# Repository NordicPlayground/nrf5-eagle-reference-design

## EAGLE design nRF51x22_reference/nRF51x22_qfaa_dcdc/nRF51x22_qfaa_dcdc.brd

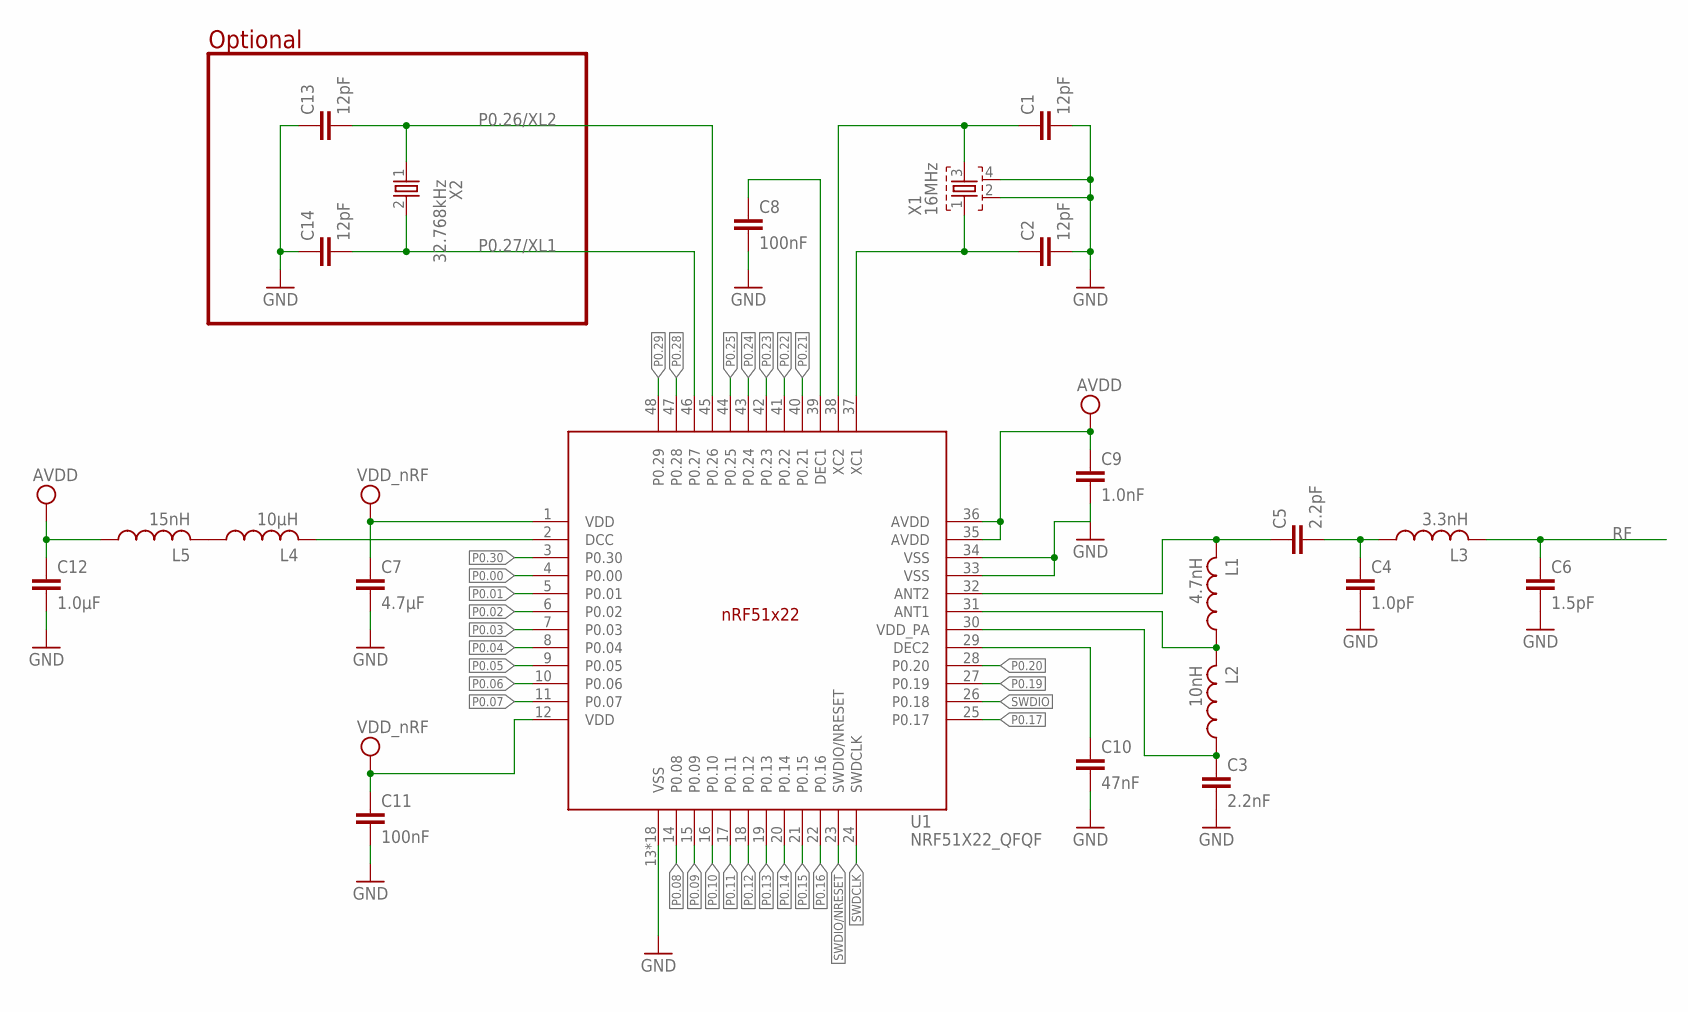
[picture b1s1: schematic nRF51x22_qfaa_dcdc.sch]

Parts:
C1, C2, C13, C14: 12pF; RESC0402_N
C3: 2.2nF; RESC0402_N
C4: 1.0pF; RESC0402_N
C5: 2.2pF; RESC0402_N
C6: 1.5pF; RESC0402_N
C7: 4.7µF; RESC0603_N
C8, C11: 100nF; RESC0402_N
C9: 1.0nF; RESC0402_N
C10: 47nF; RESC0402_N
C12: 1.0µF; RESC0603_N
L1: 4.7nH; RESC0402_N
L2: 10nH; RESC0402_N
L3: 3.3nH; RESC0402_N
L4: 10µH; RESC0603_N
L5: 15nH; RESC0402_N
U1: NRF51X22_QFQF; QFN40P600X600X90-48_N
X1: 16MHz; BT-XTAL_2016_N
X2: 32.768kHz; XTAL_3215_N

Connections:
AVDD: C9.1, C12.1, L5.1, U1.35 (AVDD), U1.36 (AVDD)
GND: C1.2, C2.2, C3.2, C4.2, C6.2, C7.2, C8.2, C9.2, C10.2, C11.2, C12.2, C13.1, C14.1, U1.13 (VSS), U1.33 (VSS), U1.34 (VSS), U1.PAD (VSS), U1.PAD@VIA01 (VSS), U1.PAD@VIA02 (VSS), U1.PAD@VIA03 (VSS), U1.PAD@VIA04 (VSS), U1.PAD@VIA05 (VSS), U1.PAD@VIA06 (VSS), U1.PAD@VIA07 (VSS), U1.PAD@VIA08 (VSS), U1.PAD@VIA09 (VSS), U1.PAD@VIA10 (VSS), U1.PAD@VIA11 (VSS), U1.PAD@VIA12 (VSS), U1.PAD@VIA13 (VSS), U1.PAD@VIA14 (VSS), U1.PAD@VIA15 (VSS), U1.PAD@VIA16 (VSS), X1.2, X1.4
unnamed: L1.1, L2.2, U1.31 (ANT1)
unnamed: L4.1, L5.2
unnamed: C1.1, U1.38 (XC2), X1.3
unnamed: L4.2, U1.2 (DCC)
unnamed: C10.1, U1.29 (DEC2)
unnamed: C8.1, U1.39 (DEC1)
unnamed: C3.1, L2.1, U1.30 (VDD_PA)
unnamed: C5.1, L1.2, U1.32 (ANT2)
unnamed: C4.1, C5.2, L3.1
P0.00: U1.4 (P0.00)
P0.01: U1.5 (P0.01)
P0.02: U1.6 (P0.02)
P0.03: U1.7 (P0.03)
P0.04: U1.8 (P0.04)
P0.05: U1.9 (P0.05)
P0.06: U1.10 (P0.06)
P0.07: U1.11 (P0.07)
P0.08: U1.14 (P0.08)
P0.09: U1.15 (P0.09)
P0.10: U1.16 (P0.10)
P0.11: U1.17 (P0.11)
P0.12: U1.18 (P0.12)
P0.13: U1.19 (P0.13)
P0.14: U1.20 (P0.14)
P0.15: U1.21 (P0.15)
P0.16: U1.22 (P0.16)
P0.17: U1.25 (P0.17)
P0.19: U1.27 (P0.19)
P0.20: U1.28 (P0.20)
P0.21: U1.40 (P0.21)
P0.22: U1.41 (P0.22)
P0.23: U1.42 (P0.23)
P0.24: U1.43 (P0.24)
P0.25: U1.44 (P0.25)
P0.26/XL2: C13.2, U1.45 (P0.26), X2.1
P0.27/XL1: C14.2, U1.46 (P0.27), X2.2
P0.28: U1.47 (P0.28)
P0.29: U1.48 (P0.29)
P0.30: U1.3 (P0.30)
RF: C6.1, L3.2
SWDCLK: U1.24 (SWDCLK)
SWDIO: U1.26 (P0.18)
SWDIO/NRESET: U1.23 (SWDIO/NRESET)
VDD_NRF: C7.1, C11.1, U1.1 (VDD), U1.12 (VDD)
X1: C2.1, U1.37 (XC1), X1.1

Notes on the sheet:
Optional

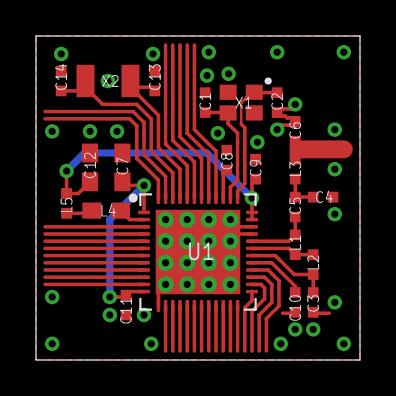
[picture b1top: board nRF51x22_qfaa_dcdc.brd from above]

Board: 2 copper layers, 18.0 x 18.0 mm, 22 parts (0 on the bottom side), 16 nets.

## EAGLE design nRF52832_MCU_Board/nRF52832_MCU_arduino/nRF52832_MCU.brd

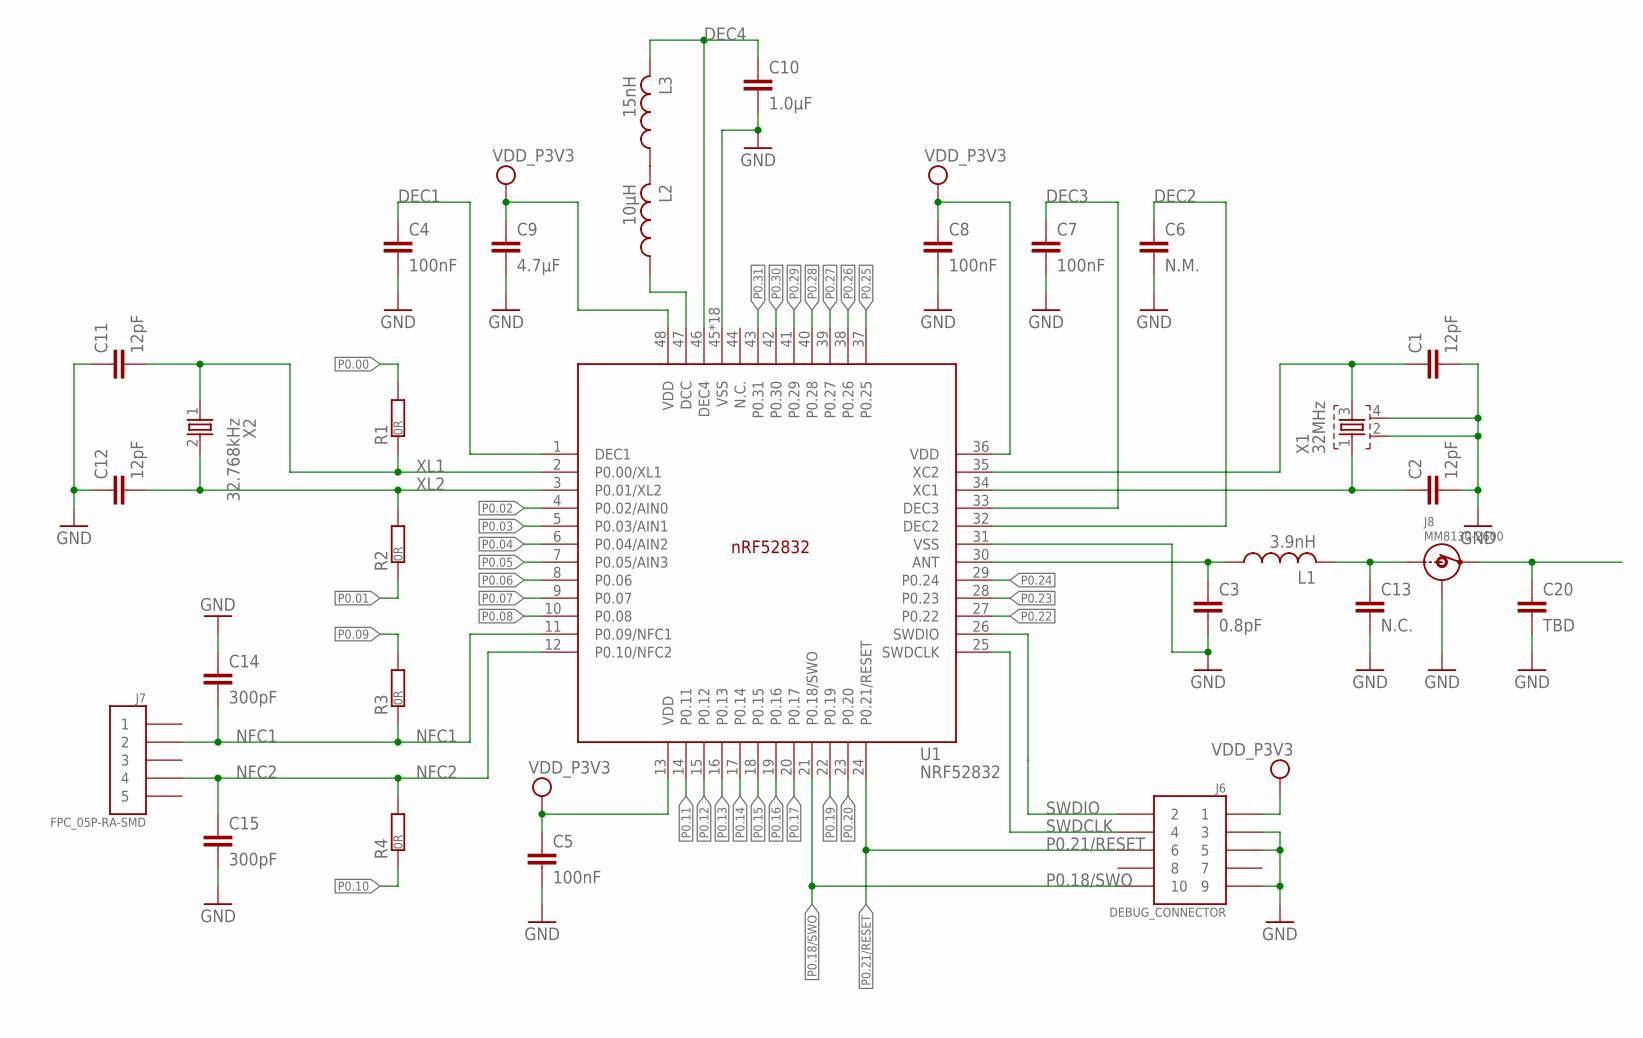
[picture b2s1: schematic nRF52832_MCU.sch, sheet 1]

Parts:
C1, C2, C11, C12: 12pF; RESC0402_N
C3: 0.8pF; RESC0402_N
C4, C5, C7, C8: 100nF; RESC0402_N
C6: N.M.; RESC0402_N
C9: 4.7µF; RESC0603_N
C10: 1.0µF; RESC0603_N
C13: N.C.; RESC0402_N
C14, C15: 300pF; RESC0402_N
C20: TBD; RESC0402_N
J6: DEBUG_CONNECTOR; HDRV127P5X2-10_N
J7: FPC_05P-RA-SMD
J8: MM8130-2600
L1: 3.9nH; RESC0402_N
L2: 10µH; RESC0603_N
L3: 15nH; RESC0402_N
R1, R2, R3, R4: 0R; RESC0402_N
U1: NRF52832; QFN40P600X600X90-48_N
X1: 32MHz; BT-XTAL_2016_N
X2: 32.768kHz; XTAL_3215_N

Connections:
ANT: C3.1, L1.1, U1.30 (ANT)
DEC1: C4.1, U1.1 (DEC1)
DEC2: C6.1, U1.32 (DEC2)
DEC3: C7.1, U1.33 (DEC3)
DEC4: C10.1, L3.2, U1.46 (DEC4)
GND: C1.2, C2.2, C3.2, C4.2, C5.2, C6.2, C7.2, C8.2, C9.2, C10.2, C11.1, C12.1, C13.2, C14.1, C15.2, C20.2, J6.3, J6.5, J6.9, J8.1, J8.2, J8.3, J8.4, U1.31 (VSS), U1.45 (VSS), U1.PAD (VSS), U1.PAD@VIA01 (VSS), U1.PAD@VIA02 (VSS), U1.PAD@VIA03 (VSS), U1.PAD@VIA04 (VSS), U1.PAD@VIA05 (VSS), U1.PAD@VIA06 (VSS), U1.PAD@VIA07 (VSS), U1.PAD@VIA08 (VSS), U1.PAD@VIA09 (VSS), U1.PAD@VIA10 (VSS), U1.PAD@VIA11 (VSS), U1.PAD@VIA12 (VSS), U1.PAD@VIA13 (VSS), U1.PAD@VIA14 (VSS), U1.PAD@VIA15 (VSS), U1.PAD@VIA16 (VSS), X1.2, X1.4; also elsewhere on the board
unnamed: C20.1, J8.OUT
unnamed: L2.2, L3.1
unnamed: C1.1, U1.35 (XC2), X1.3
unnamed: L2.1, U1.47 (DCC)
unnamed: C13.1, J8.IN, L1.2
NFC1: C14.2, J7.2, R3.1, U1.11 (P0.09/NFC1)
NFC2: C15.1, J7.4, R4.2, U1.12 (P0.10/NFC2)
P0.00: R1.2
P0.01: R2.1
P0.02: U1.4 (P0.02/AIN0)
P0.03: U1.5 (P0.03/AIN1)
P0.04: U1.6 (P0.04/AIN2)
P0.05: U1.7 (P0.05/AIN3)
P0.06: U1.8 (P0.06); also elsewhere on the board
P0.07: U1.9 (P0.07); also elsewhere on the board
P0.08: U1.10 (P0.08); also elsewhere on the board
P0.09: R3.2
P0.10: R4.1
P0.11: U1.14 (P0.11)
P0.12: U1.15 (P0.12)
P0.13: U1.16 (P0.13)
P0.14: U1.17 (P0.14)
P0.15: U1.18 (P0.15)
P0.16: U1.19 (P0.16)
P0.17: U1.20 (P0.17)
P0.18/SWO: J6.10, U1.21 (P0.18/SWO)
P0.19: U1.22 (P0.19)
P0.20: U1.23 (P0.20)
P0.21/RESET: J6.6, U1.24 (P0.21/RESET); also elsewhere on the board
P0.22: U1.27 (P0.22)
P0.23: U1.28 (P0.23)
P0.24: U1.29 (P0.24)
P0.25: U1.37 (P0.25)
P0.26: U1.38 (P0.26)
P0.27: U1.39 (P0.27)
P0.28: U1.40 (P0.28)
P0.29: U1.41 (P0.29)
P0.30: U1.42 (P0.30)
P0.31: U1.43 (P0.31)
SWDCLK: J6.4, U1.25 (SWDCLK)
SWDIO: J6.2, U1.26 (SWDIO)
VDD_P3V3: C5.1, C8.1, C9.1, J6.1, U1.13 (VDD), U1.36 (VDD), U1.48 (VDD); also elsewhere on the board
X1: C2.1, U1.34 (XC1), X1.1
XL1: C11.2, R1.1, U1.2 (P0.00/XL1), X2.1
XL2: C12.2, R2.2, U1.3 (P0.01/XL2), X2.2

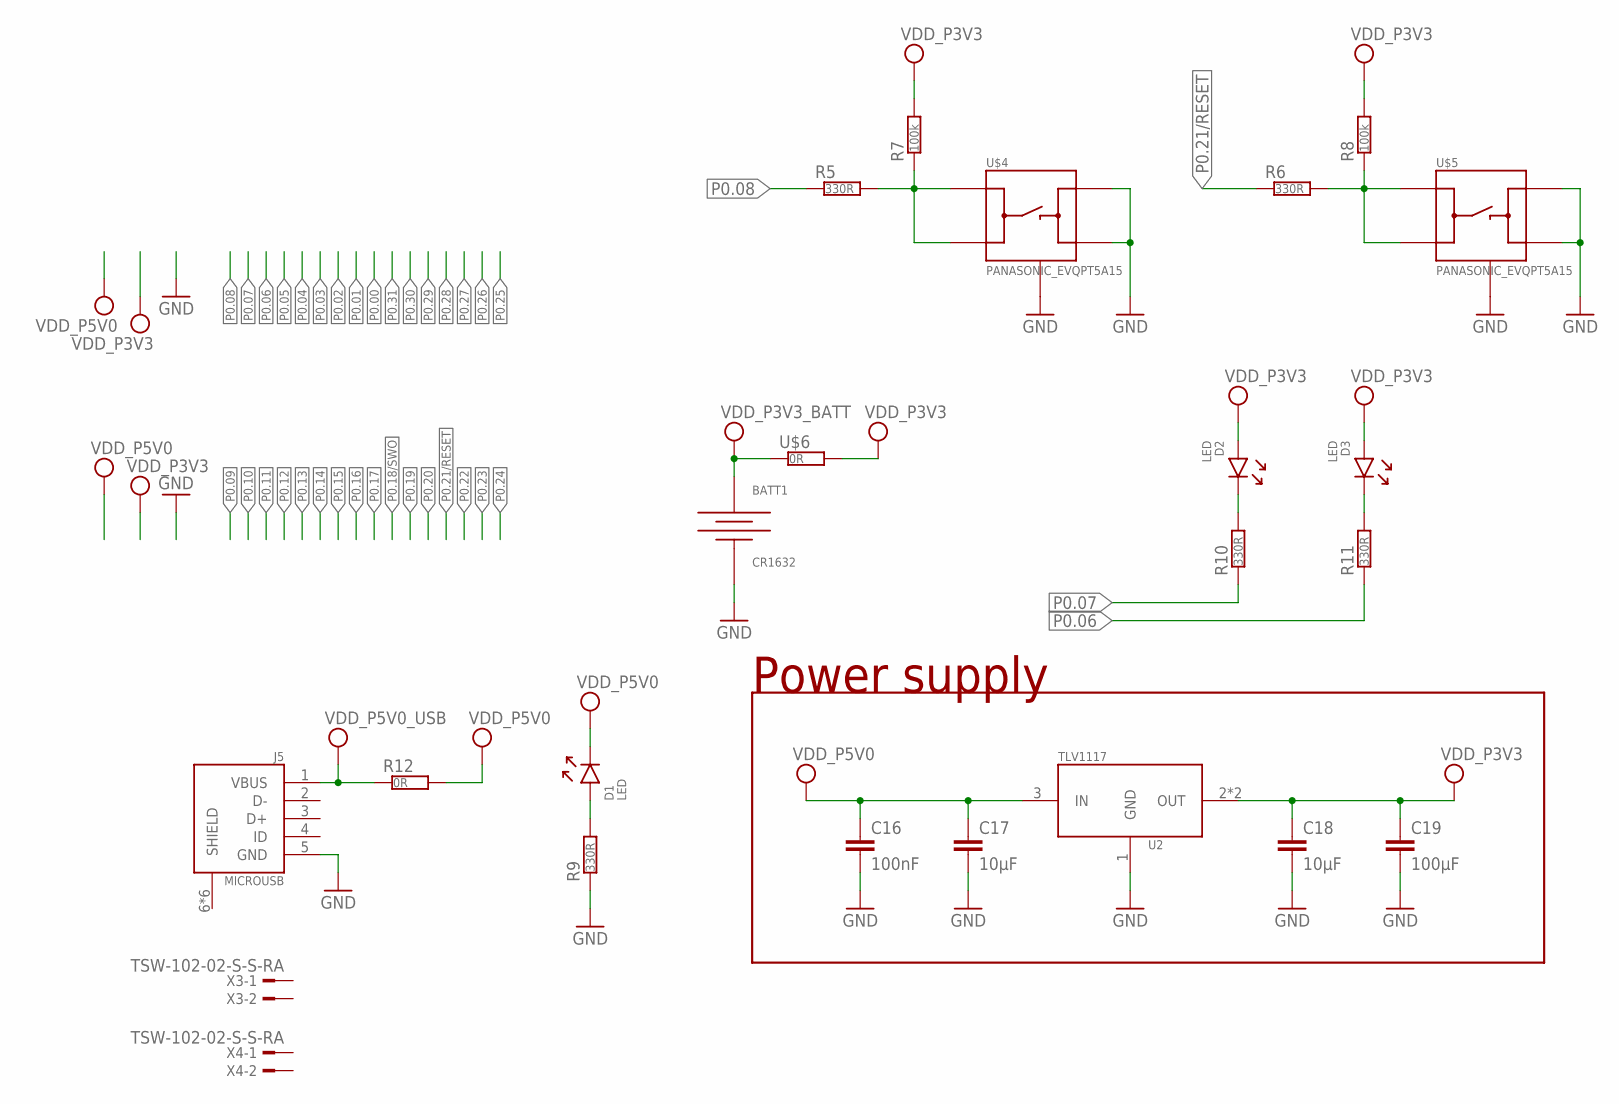
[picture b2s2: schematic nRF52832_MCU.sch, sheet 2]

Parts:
BATT1: CR1632; CR1632_HOLDER_TH
C16: 100nF; RESC0402_N
C17, C18: 10µF; RESC0603_N
C19: 100µF; RESC0805_N
D1, D2, D3: LED; DIOC0603_N
J5: MICROUSB; USB-MICRO-B-RA-SMD-PIP
R5, R6, R9, R10, R11: 330R; RESC0402_N
R7, R8: 100k; RESC0402_N
R12: 0R; RESC0402_N
U2: TLV1117; SOT220P700-4_N
U$4, U$5: PANASONIC_EVQPT5A15
U$6: 0R; RESC0402_N
X3, X4: TSW-102-02-S-S-RA

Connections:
GND: BATT1.1 (-), C16.2, C17.2, C18.2, C19.2, J5.5 (GND), R9.1, U2.1 (GND), U$4.3 (B), U$4.4 (B'), U$4.5 (GND), U$4.6 (GND), U$5.3 (B), U$5.4 (B'), U$5.5 (GND), U$5.6 (GND); also elsewhere on the board
unnamed: R6.2, R8.1, U$5.1 (A), U$5.2 (A')
unnamed: R5.2, R7.1, U$4.1 (A), U$4.2 (A')
unnamed: D2.1 (C), R10.2
unnamed: D3.1 (C), R11.2
P0.06: R11.1; also elsewhere on the board
P0.07: R10.1; also elsewhere on the board
P0.08: R5.1; also elsewhere on the board
P0.21/RESET: R6.1; also elsewhere on the board
VCC_P5V0_USB: J5.1 (VBUS), R12.1
VDD_LED: D1.2 (A), R9.2
VDD_P3V3: C18.1, C19.1, D2.2 (A), D3.2 (A), R7.2, R8.2, U2.2 (OUT), U2.4 (OUT), U$6.2; also elsewhere on the board
VDD_P3V3_BATT: BATT1.2 (+), BATT1.3 (+), U$6.1
VDD_P5V0: C16.1, C17.1, D1.1 (C), R12.2, U2.3 (IN)

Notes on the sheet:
Power supply

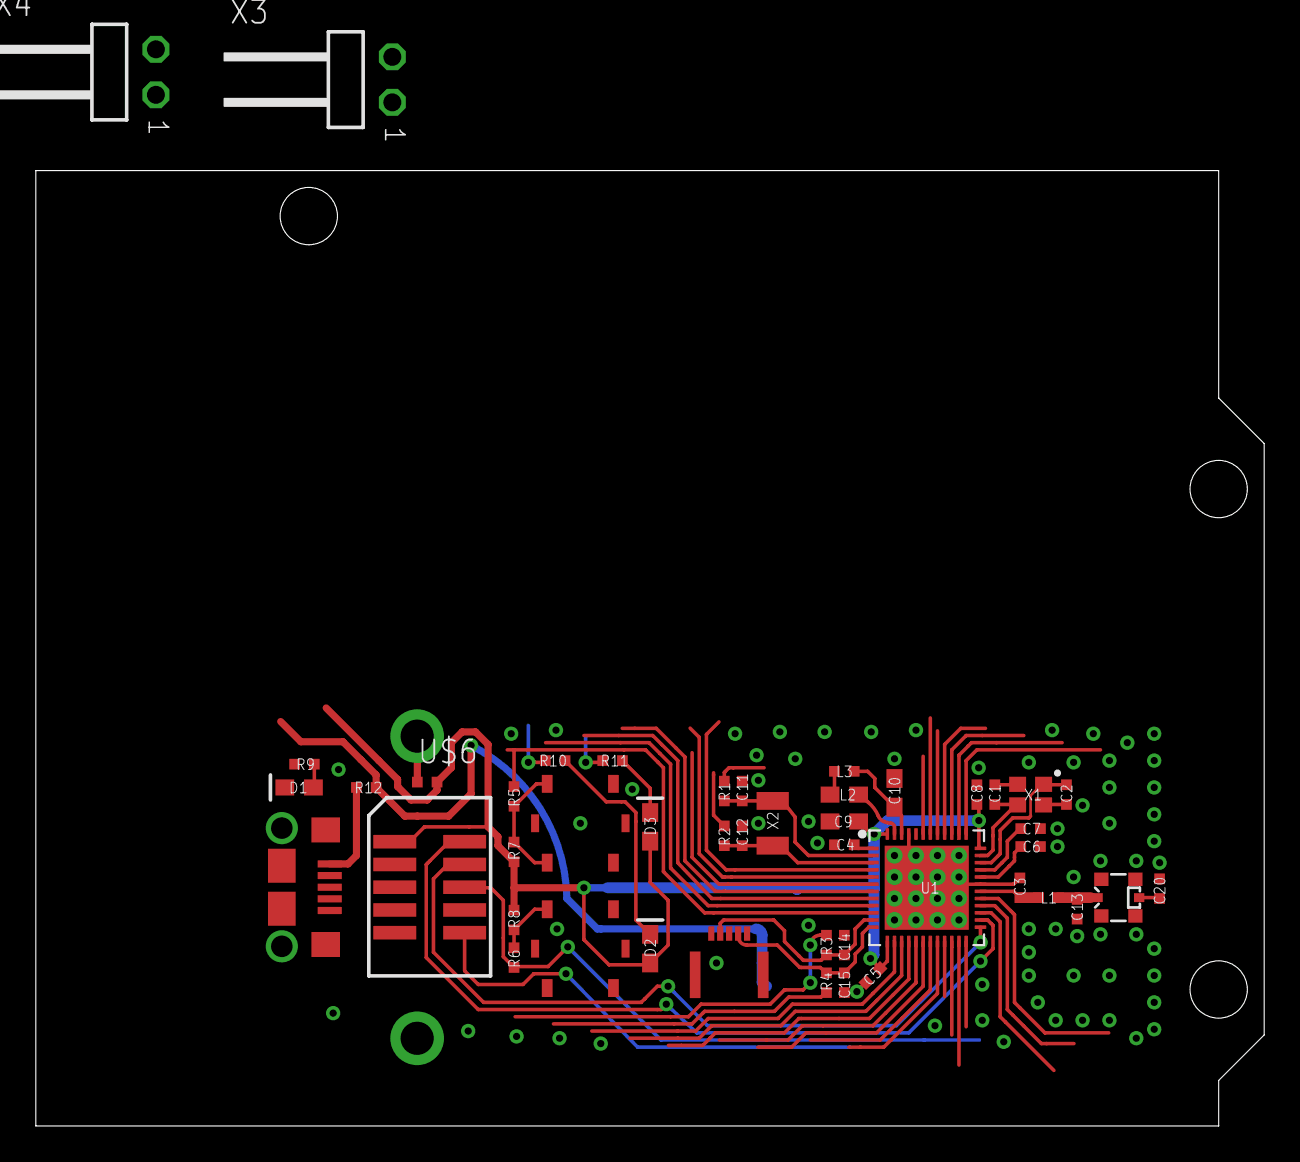
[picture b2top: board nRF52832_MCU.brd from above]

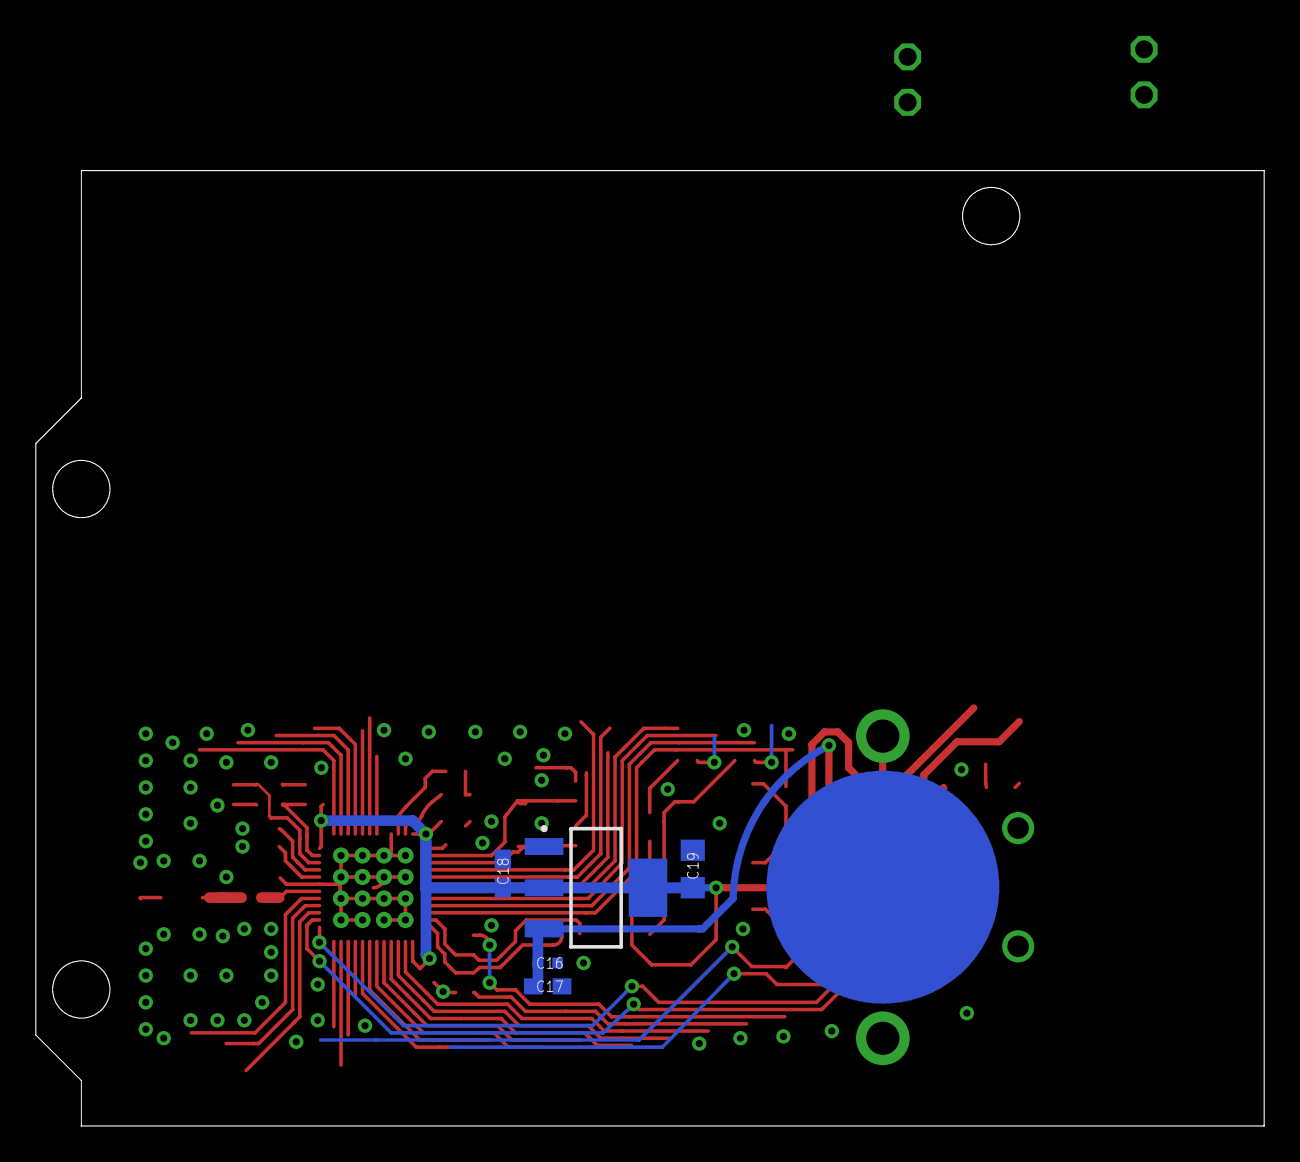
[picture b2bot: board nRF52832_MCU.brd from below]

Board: 2 copper layers, 68.6 x 53.3 mm, 52 parts (6 on the bottom side), 32 nets.

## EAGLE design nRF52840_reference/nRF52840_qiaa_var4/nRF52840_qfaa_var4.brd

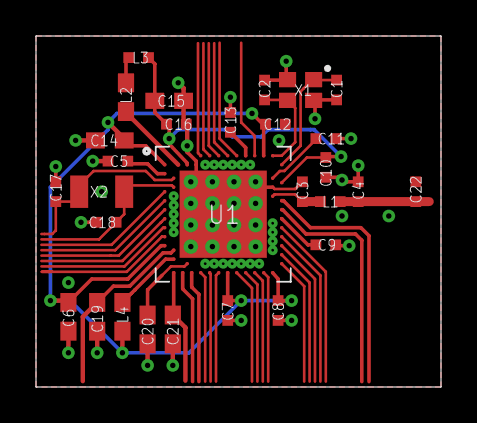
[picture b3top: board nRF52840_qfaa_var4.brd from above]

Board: 4 copper layers, 22.5 x 19.5 mm, 29 parts (0 on the bottom side), 19 nets.

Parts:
C1, C2, C17, C18: 12pF; RESC0402_N
C3, C4: 1pF; RESC0402_N
C5, C7, C8, C12: 100nF; RESC0402_N
C6, C14, C19, C20, C21: 4.7µF; RESC0603_N
C9: 820pF; RESC0402_N
C10, C13, C22: N.C.; RESC0402_N
C11: 100pF; RESC0402_N
C15: 1.0µF; RESC0603_N
C16: 47nF; RESC0402_N
L1: 3.9nH; RESC0402_N
L2, L4: 10µH; RESC0603_N
L3: 15nH; RESC0402_N
U1: NRF52840_QF; AQFN50P700X700X85_HS-74N
X1: 32MHz; BT-XTAL_2016_N
X2: 32.768kHz; XTAL_3215_N

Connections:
ANT: C3.1, L1.1, U1.P$H23
DCC: L2.1, U1.P$B3
DEC1: C5.1, U1.P$C1
DEC2: C13.1, U1.P$A18
DEC3: C11.1, U1.P$D23
DEC3V3: C20.1, U1.P$AC5
DEC4_6: C10.1, C15.1, C16.1, L3.2, U1.P$B5, U1.P$E24
DEC5: C9.1, U1.P$N24
GND: C1.2, C2.2, C3.2, C4.2, C5.2, C6.2, C7.2, C8.2, C9.2, C10.2, C11.2, C12.2, C13.2, C14.2, C15.2, C16.2, C17.1, C18.1, C19.2, C20.2, C21.2, C22.2, U1.P$74, U1.P$75, U1.P$76, U1.P$77, U1.P$78, U1.P$79, U1.P$80, U1.P$81, U1.P$82, U1.P$83, U1.P$84, U1.P$85, U1.P$86, U1.P$87, U1.P$88, U1.P$89, U1.P$90, U1.P$B7, U1.P$F23, X1.2, X1.4
unnamed: L4.2, U1.P$AB2
unnamed: L2.2, L3.1
P0.00/XL1: C17.2, U1.P$D2, X2.1
P0.01/XL2: C18.2, U1.P$F2, X2.2
RF: C4.1, C22.1, L1.2
VBUS: C21.1, U1.P$AD2
VDD_HV: C19.1, U1.P$Y2
VDD_P3V3: C6.1, C7.1, C8.1, C12.1, C14.1, L4.1, U1.P$A22, U1.P$AD14, U1.P$AD23, U1.P$B1, U1.P$W1
XC1: C1.1, U1.P$B24, X1.1
XC2: C2.1, U1.P$A23, X1.3
